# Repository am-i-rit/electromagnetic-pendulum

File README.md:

# electromagnetic-pendulum
attempt at a hardware project, gonna design a pcb, cad the structure, and write some firmware

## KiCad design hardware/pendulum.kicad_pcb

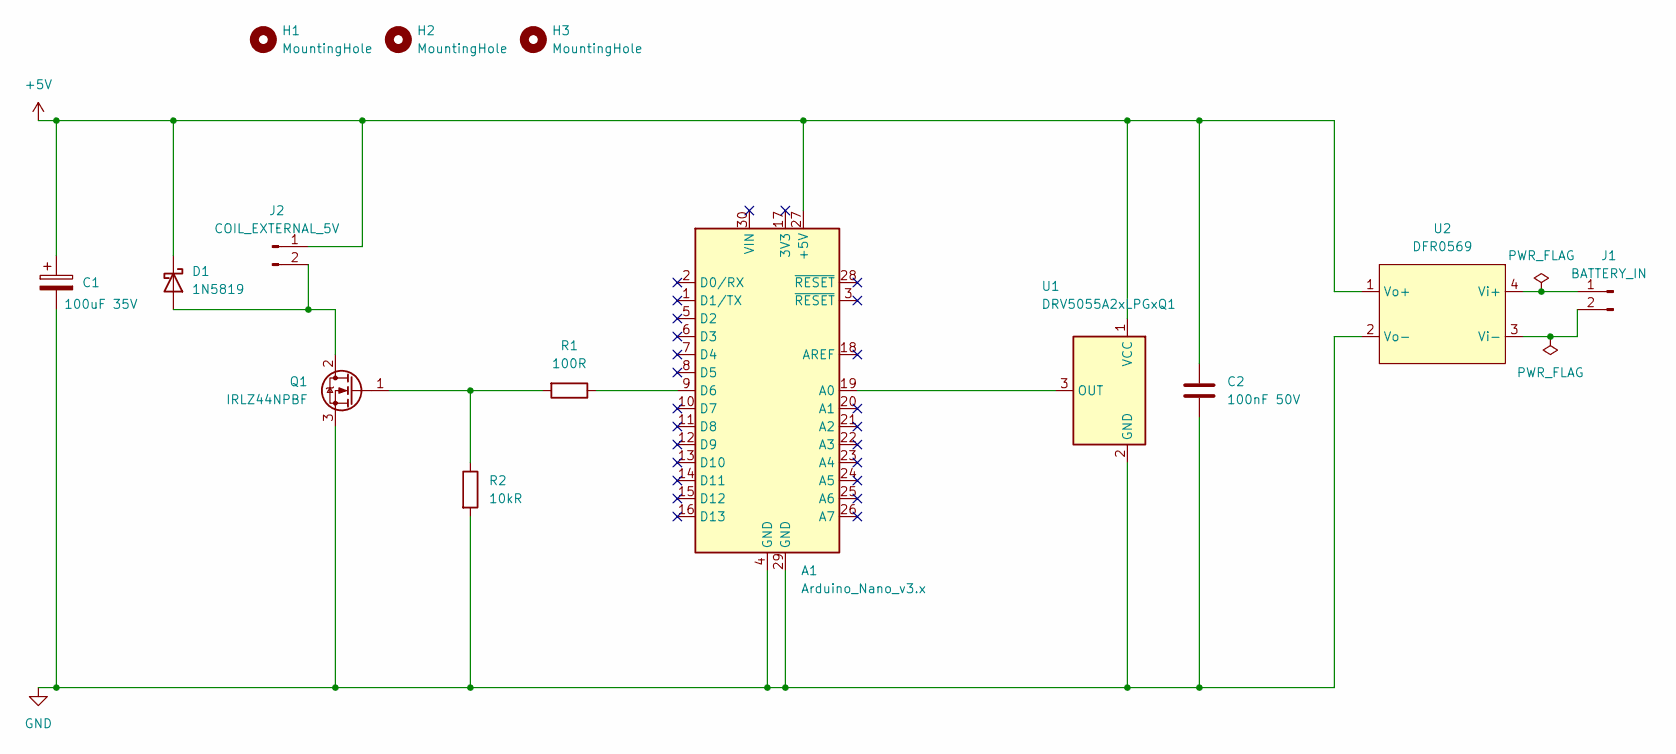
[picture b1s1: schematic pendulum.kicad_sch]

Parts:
A1: Arduino_Nano_v3.x; Arduino_Nano
C1: 100uF 35V; CP_Radial_D6.3mm_P2.50mm
C2: 100nF 50V; C_Rect_L4.6mm_W3.0mm_P2.50mm_MKS02_FKP02
D1: 1N5819; D_DO-41_SOD81_P10.16mm_Horizontal
H1, H2, H3: MountingHole; MountingHole_3.2mm_M3
J1: BATTERY_IN; TerminalBlock_Phoenix_MKDS-1,5-2-5.08_1x02_P5.08mm_Horizont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
J2: COIL_EXTERNAL_5V; TerminalBlock_Phoenix_MKDS-1,5-2-5.08_1x02_P5.08mm_Horizont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
Q1: IRLZ44NPBF; TO-220-3_Vertical
R1: 100R; R_Axial_DIN0207_L6.3mm_D2.5mm_P7.62mm_Horizontal
R2: 10kR; R_Axial_DIN0207_L6.3mm_D2.5mm_P7.62mm_Horizontal
U1: DRV5055A2xLPGxQ1; TO-92_Inline
U2: DFR0569

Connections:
+5V: A1.27 (+5V), C1.1, C2.1, D1.1 (K), J2.1, U1.1 (VCC), U2.1 (Vo+)
GND: A1.4 (GND), A1.29 (GND), C1.2, C2.2, Q1.3 (S), R2.2, U1.2 (GND), U2.2 (Vo-)
unnamed: A1.19 (A0), U1.3 (OUT)
unnamed: A1.9 (D6), R1.1
unnamed: D1.2 (A), J2.2, Q1.2 (D)
unnamed: J1.1, U2.4 (Vi+)
unnamed: J1.2, U2.3 (Vi-)
unnamed: Q1.1 (G), R1.2, R2.1

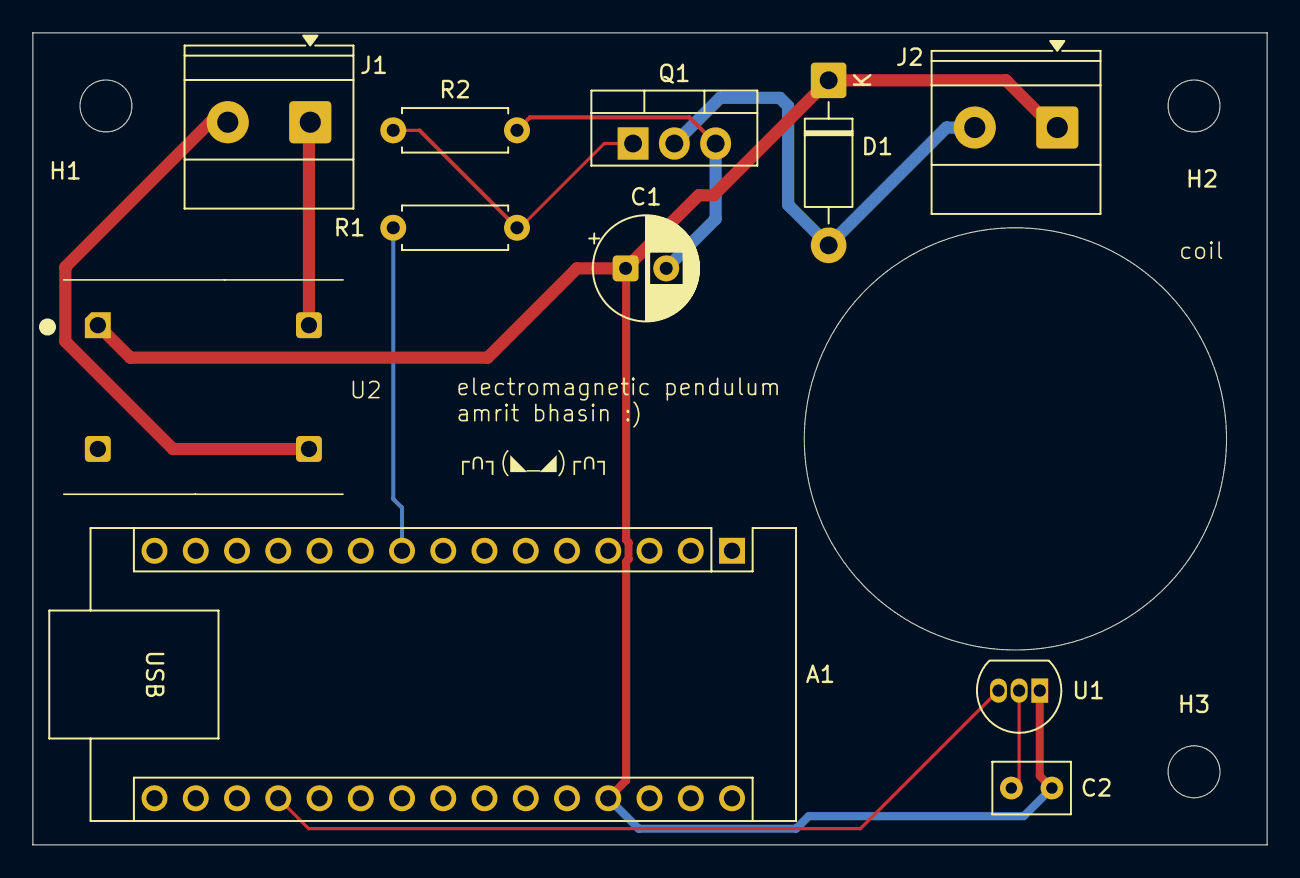
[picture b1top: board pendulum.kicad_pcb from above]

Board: 2 copper layers, 76.0 x 50.0 mm, 14 parts (0 on the bottom side), 8 nets.
